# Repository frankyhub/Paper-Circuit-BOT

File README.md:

<div align="center">

|[:skull:ISSUE](https://github.com/frankyhub/Paper-Circuit-BOT/issues?q=is%3Aissue)|[:speech_balloon: Forum /Discussion](https://github.com/frankyhub/Paper-Circuit-BOT/discussions)|[:grey_question:WiKi](https://github.com/frankyhub/Paper-Circuit-BOT/wiki)||
|--|--|--|--|
| | | | |
<a href="https://github.com/frankyhub/Paper-Circuit-BOT/issues">|<a href="https://github.com/frankyhub/Paper-Circuit-BOT/discussions">|<a href="https://github.com/frankyhub/Paper-Circuit-BOT/releases">||
|| <a href="https://github.com/frankyhub/Paper-Circuit-BOT/pulse" alt="Activity">| <a href="https://github.com/frankyhub/Paper-Circuit-BOT/graphs/traffic">  |<a href="https://github.com/frankyhub?tab=stars"> ||

</div>

## Paper-Circuit-Bot mit 2 LEDs

<br> <br>

## Die einzelnen Schritte:

+ Schneide den gesamten Grundkörper aus.

<br> <br>

+ Schneide die Druckvorlage aus.

<br> <br>

+ Stanze die Löcher für die 5mm LEDs aus.

+ Klebe die Kupferleiterbahnen auf die Vorlage, verbinde den 33R Widerstand und befestige die beiden LEDs. Das kurze Bein der LED zeigt nach oben zu K.

<br> <br>

<br> <br>

+ Befestige die Batterie mit zwei Klebestreifen. Der Plus-Pol zeigt nach oben.

<br> <br>

+ Stanze die Löcher für die 5mm LEDs aus dem Grundkörper aus.

+ Klebe die Druckvorlage in die Innenseite des Grundkörpers

<br> <br>

+ Knicke den oberen Teil der Druckvorlage diagonal ein und stelle mit der Klammer den Kontakt zur Batterie her, das ist unser Schalter.

<br> <br>

+ Führe einen Funktionstest durch.

+ Falte den Grundkörper an den gestrichelten Linien und verklebe den Kopf an den Falzstellen.

+ Verklebe den Kopf, den Body und die Füße.

  ---

## BOM

| Stück | Bezeichnung |
| -------- | -------- | 
| 1        |   [Druckvorlage](/pdf/Bot-Druckvorlage.pdf)    |
| 1        |  [BOT-Vorlage](/pdf/MetalBot2.pdf)    |
| 1        | CR2032       | 
| 2        | LED 5mm rot        | 
| 1        | R 33       | 
| 1        | CU-Band       |
| 1        | Binder Clip 25mm       |
| 1        | Kleber     |

---

## Und fertig ist der kleine BOT 

<br> <br>

---

<div style="position:absolute; left:2cm; ">   
<ol class="breadcrumb" style="border-top: 2px solid black;border-bottom:2px solid black; height: 45px; width: 900px;"> <p align="center"><a href="#oben">nach oben</a></p></ol>
</div>

---

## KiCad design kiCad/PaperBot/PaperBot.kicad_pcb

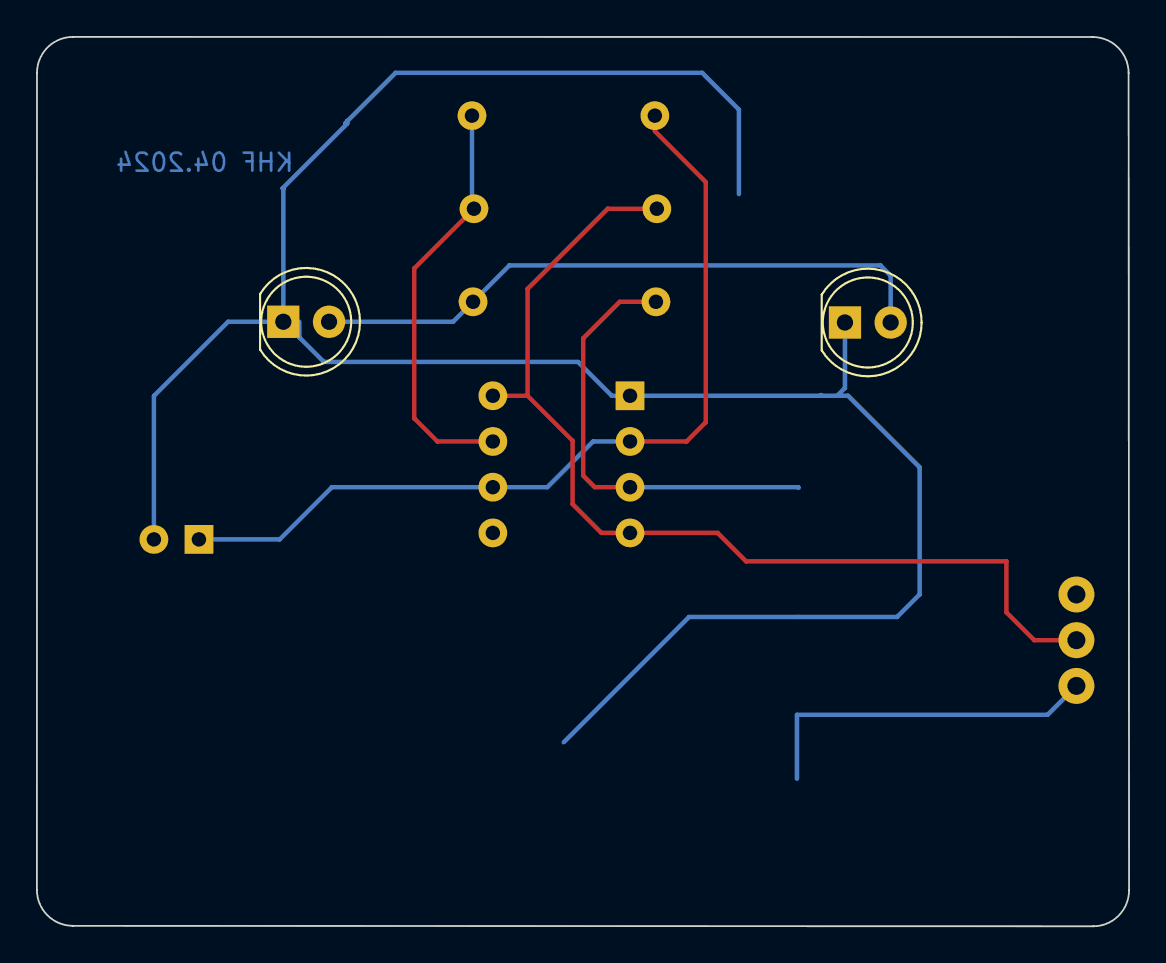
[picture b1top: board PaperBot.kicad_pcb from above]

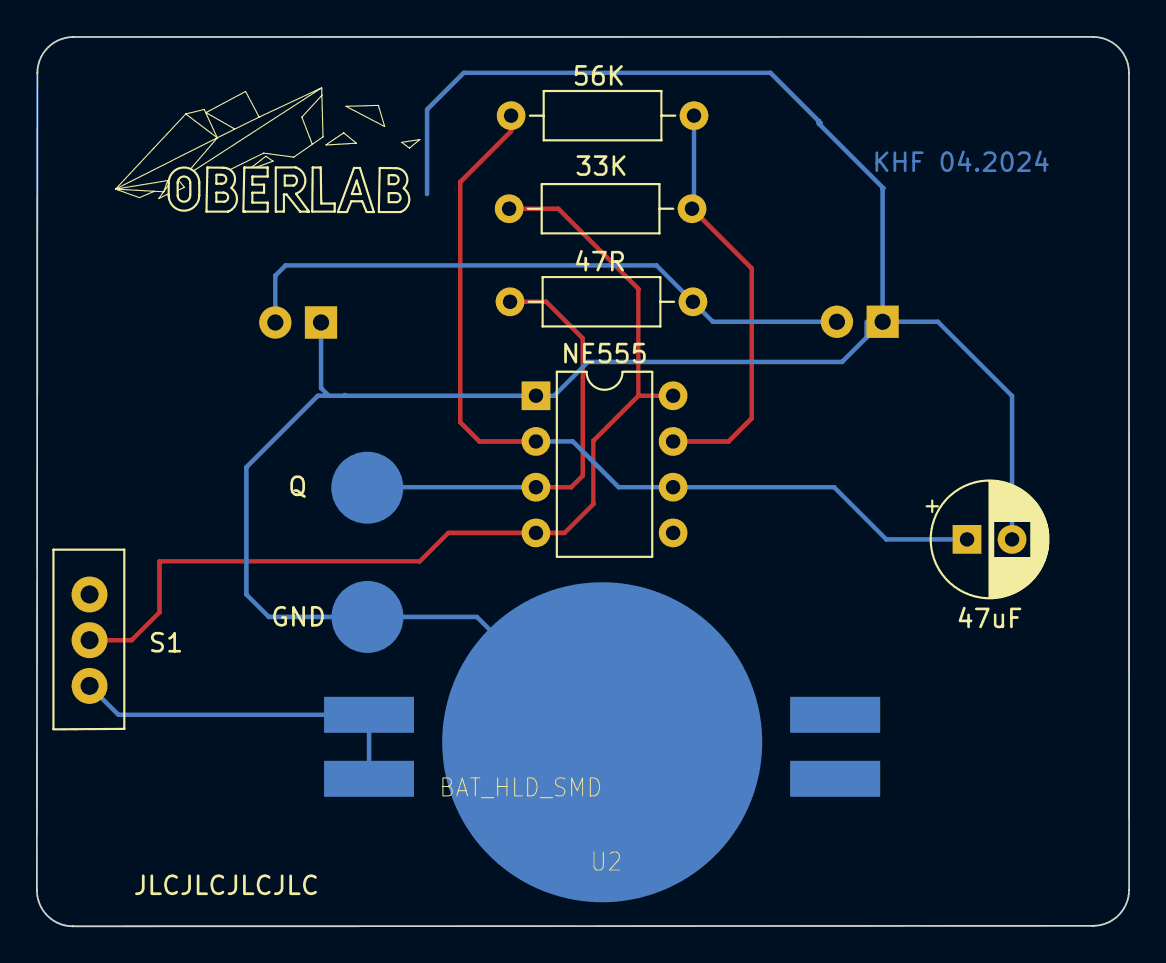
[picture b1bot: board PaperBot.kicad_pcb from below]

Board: 2 copper layers, 60.7 x 49.4 mm, 10 parts (8 on the bottom side), 6 nets.

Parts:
C1: 47uF; CP_Radial_D6.3mm_P2.50mm
D1, D2: LED; LED_D5.0mm
GND: Q; LP
NE555: NE555P; DIP-8_W7.62mm
R1: 56K; R_Axial_DIN0207_L6.3mm_D2.5mm_P10.16mm_Horizontal
R2: 33K; R_Axial_DIN0207_L6.3mm_D2.5mm_P10.16mm_Horizontal
R3: 47R; R_Axial_DIN0207_L6.3mm_D2.5mm_P10.16mm_Horizontal
S1: Micro_Schalter; Micro_SchalterKHF
U2: BAT_HLD_SMD; BAT-HLD-SMD-Blech

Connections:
unnamed: D1.2 (A), D2.2 (A), R3.2
unnamed: C1.2, D1.1 (K), D2.1 (K), GND.1, NE555.1 (GND), U2.2
unnamed: NE555.4 (R), NE555.8 (VCC), R2.1, S1.2 (E)
unnamed: NE555.7 (DIS), R1.2, R2.2
unnamed: NE555.3 (Q), R3.1
unnamed: C1.1, NE555.2 (TR), NE555.6 (THR), R1.1

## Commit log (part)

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2024-02-01 V1.0
2024-02-01 V1.1
2024-02-01 V1.2
2024-02-01 Rename Bot+Circuit.png to BotCircuit.png
2024-02-01 V1.3
2024-02-01 Rename Druckvorlage-Bot.svg to BOT-Druckvorlage.svg
2024-02-01 Rename Druckvorlage-Bot.pdf to Bot-Druckvorlaget.pdf
2024-02-01 Rename Bot-Druckvorlaget.pdf to Bot-Druckvorlage.pdf
2024-05-10 V 10.05.2024
2024-05-18 V 18.05.2024
2024-05-22 V 22.05.2024
2024-10-12 V12102024
